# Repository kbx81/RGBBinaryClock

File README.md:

# kbx's RGB Binary Clock

RGB Binary Clock project files - PCB and source

_It's probably more than what you're thinking..._

## Another binary clock? Why?

I have to start by giving credit where credit is due. The
 [Boldport Club](http://boldport.club), over the last couple of years, has
 motivated me to dwell back into the world of electronics, at least as a
 hobbyist. Both the kits themselves and the other members in the club are
 amazing and helped inspire me to make something...so I began working on this
 project. Some inspiration is taken from
 [Touchy, BPC Project #7](https://www.boldport.com/products/touchy); this kit
 enabled me to learn more about and actually experiment with capacitive touch.
 It was clear early on that this would be a nice touch (pun intended) to add to
 this project; visually, it is cleaner, it reduces the number of parts and, as a
 result, it reduces the cost.

That said, the world probably doesn't need another (binary) clock. There are
 plenty of them--all different shapes and sizes--so why build another one?

This project was started with two main goals in mind: I wanted a "simple"
 project I could use to help me get back into the world of electronics. The
 second goal I had in mind was to build up my comfort level with C and C++ -- I
 knew the language(s) but was never terribly comfortable with them. Building
 this helped me to achieve both of those goals and then some -- and I am quite
 happy with the result!

_But why a clock?_

It's fun to make LEDs blink. It's fun to play with microcontrollers. It's fun
 to build stuff. But a blinking LED or two or three isn't very meaningful. Nor
 is a nice microcontroller that just toggles a GPIO pin. If you're going to
 build something, why not make it at least modestly useful? And why not build it
 in a unique way that's neat to look at and/or watch?

The idea for this came from an old electronics kit I put together probably
 around twenty or so years ago (and it still works today!). I liked the kit but
 it was somehow lacking. Probably the most obvious problem was that, in a dark
 bedroom, the display was too bright. It was a simple, 12-hour-only binary
 clock, built on 4000-series CMOS logic. Now, there's nothing wrong with that,
 but...it's 2018 now. Let's take it up a notch or ten.

## How do you take a binary clock up a notch (or ten)?

First, you can add some color. A lot of color. In fact, you can pick the colors
 you want it to use...up to eight times over. This binary clock has the ability
 to gradually shift colors over the course of each day. Bits can even fade in
 and out as they change. It's all about the eye candy in this regard.

Second, it can do more than just tell the time -- it'll tell you the date and
 temperature, too! There is even a timer/counter mode. What's more, you can
 choose the format for it all: the clock can display in a 12 or 24 hour format,
 the temperature can display in degrees Celsius or degrees Fahrenheit, and (most
 importantly) it can display all of these values in either binary-coded decimal
 (BCD) or good old-fashioned binary. You get to choose the formats you prefer
 and they can be changed easily at any time.

Next, the display brightness issue had to be addressed -- it has a
 phototransistor which is used to determine the amount of ambient light around
 it and the display will dim as the light level around it diminishes. This is
 great if you want to keep it near you at night while you sleep.

Another cool bit is that it uses capacitive sense touch keys for buttons; the
 kit it is based on had mechanical, fixed-function buttons. If you haven't seen
 or used capsense technology before, you'll find it's pretty cool and adds a
 little extra uniqueness to the clock, too.

A CR2032 coin-cell battery back-up can be installed to keep the time valid in
 the event that the board loses power. Version 4 of the hardware also includes a
 super capacitor, eliminating the need for the battery; even so, both can be
 installed, adding flexibility to the build.

Finally--and one could argue that no clock is complete without one--it has an
 alarm! The alarm can be set to beep at any of the eight times the user sets.
 There is also an hourly chime that one can enable which will beep out each hour
 in binary using high and/or low pitch tones...so you can hear the time when
 you're in another room! The display can be configured to blink when an alarm
 occurs. Version 4 of the clock also includes extra pin headers, some pins of
 which can be used as inputs to trigger the alarm from an external device.

## Great, but what makes it tick?

The "brain" is an STM32F072 microcontroller. This MCU alone has everything
 that's necessary to have a functional time clock -- even a temperature sensor
 as a bonus. Still, it might not be quite as accurate as some of us would like.
 For those folks, there are footprints for some additional ICs to improve the
 accuracy of the time and/or temperature sensing.

Version 2 boards have footprints for I2C devices:
* A Maxim DS3231
* An LM75 (or compatible)
* A Microchip MCP9808

Version 3+ boards have footprints for SPI devices:
* A Maxim DS3234
* An LM74
* A Maxim DS1722

Why footprints for both temperature sensors and the RTCs? The DS323x is somewhat
 expensive and it's possible that one might want more accurate temperature
 sensing abilities but isn't as concerned with the accuracy of the clock. It
 should be noted that the DS323x devices have temperature sensors built in and
 the application will use this sensor if a DS323x is installed but one of the
 other external temperature sensors is not.

Beyond the MCU itself, the board has 25 RGB LEDs on it; 24 of them form the main
 display and they are connected to TLC5947 (pre-v4) or TLC5951 (v4+)
 constant-current PWM drivers. The MCU uses its SPI1 to communicate with these
 drivers. The remaining RGB LED is used as a "status" LED and it is connected
 (through FET drivers) to GPIO pins on the MCU. These pins double as timer
 output channels, meaning they can also generate a PWM signal, enabling the
 dimming of the status LED elements, as well.

The beeper is connected (also through a FET driver) to yet another GPIO pin
 that doubles as a timer output channel; this enables the beeper to generate a
 wide range of tones or even play a tune!

The phototransistor is connected to the MCU's ADC channel zero.

Two USARTs are exposed via pin headers on the right side of the board: USART1
 is brought out on a standard six pin header as is commonly found on many
 devices while USART2 is connected to an RS-485 line driver enabling
 communication on an RS-485 bus. Through this interface, the application is able
 to receive a DMX-512 signal so the LEDs can each be individually controlled
 from an entertainment lighting console (or other application that speaks this
 protocol), enabling another whole realm of possibilities...

## How do I get or build one?

In this repository you'll find everything needed to put one together. It is
 divided into two major parts: hardware and software (source). The `hardware`
 directory contains the [KiCad](http://kicad.org) project files used to create
 the printed circuit board. The `src` directory contains the source code needed
 to compile and run the application on the microcontroller. It is built on top
 of [libopencm3](http://libopencm3.org). Finally, then `bin` directory contains
 compiled binary files you may flash directly onto the microcontroller...great
 for folks who want to solder something together but don't want to be bothered
 with compiling code!

Additional details regarding the hardware and software can be found in the
 `README.md` files located in each respective directory.

 **That's all for now...thanks for visiting!**

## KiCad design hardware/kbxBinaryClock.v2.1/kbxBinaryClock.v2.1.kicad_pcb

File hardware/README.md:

# kbx's RGB Binary Clock

RGB Binary Clock PCB project files for KiCad (v4/v5)

## How do I get PCBs made for this?

Detailing the process is a bit outside of what I plan to discuss here. There are
 plenty of resources out around the web already that will do a better job of
 explaining this process than I can. That said, there's not much to it -- the
 files you need are here and all you need to do (more or less) is upload them
 to your PCB fabricator of choice and, after a few days, they'll ship them
 to you. I've used [OSHPark](http://oshpark.com) for the prototypes and I can
 assure you that they turn out fantastic (purple) boards.

As the vast majority of the components on this board are surface-mount parts,
 hot air is a fun approach for soldering it all together. If you go this route
 (and especially if you plan to build more than one of them), you'll likely want
 to have a stencil made to help with the placement of solder paste onto the
 board. I've used [OSHStencils](http://oshstencils.com) for this and they are
 very quick and do a wonderful job.

**Important**: The TLC5947 and TLC5951 LED driver ICs have a thermal relief (aka
 exposed) pad on their underside; this will not be possible to solder without a
 hot air soldering station or reflow oven. At low current/intensity levels, this
 shouldn't be a problem, but if you want your LEDs to be really bright, this
 could present an issue as the drivers will overheat quickly. Be careful!

## If I get boards made, how do I build it?

All the components are listed in the KiCad project files here; one can also find
 a bill of materials file named `kbxBinaryClock.bom.vX.csv` containing this
 list. For "unusual" parts (things that aren't resistors or capacitors) I've
 noted a suggested part number that should serve as a point of reference to help
 you find your own.

Before you order parts, be sure to read through the build notes below!

Once you have your boards and parts, there are at least a couple of different
 ways you can build the clock. Below are build notes.

## Build notes

### Before you begin...

...you need to determine:
1. Which version of the clock will you build? The answer should be "version 4"
 unless there is a specific reason you want/need an earlier version.
1. What will your time source be -- the STM32's RTC or the DS323x? The DS323x
 will provide the best accuracy. That said, these ICs add approximately $10 USD
 to the cost of the device. If you're purchasing them, be sure you're ordering
 the one that matches the version of the hardware you're planning on building!
1. What temperature sensor will you use -- the STM32's internal sensor, the
 DS323x's sensor, or a dedicated sensor? The DS1621/LM75/MCP9804/DS1722/LM74
 dedicated sensors will provide the best accuracy; however, if one of these ICs
 is not installed but a DS323x *is* installed, the app will use the DS323x's
 sensor. Note that, while the PCBs have footprints for more than one temperature
 sensor, only **one** of them may be installed at a time.
1. Solder-bridge/jumper settings. These are hardware version specific but *must*
 be set properly before you begin using the clock. More details are below...but
 don't forget about these!

Once you've settled on the items above, read on (below) for more detail and
 specifics regarding the build.

### Build details

#### External RTC:

The external RTC--the DS3231 (hardware version 2.x) or the DS3234 (hardware
 version 3.x+)--adds a level of precision to the clock that is likely difficult
 to achieve with the STM32's internal RTC alone. These RTC ICs are designed to
 drift less than two minutes _per year_. It's possible that your STM32 hardware
 could end up being this accurate, but it's more likely that it will not be.
 Install this IC if you want a clock that is as accurate as is reasonably
 possible. Note that this IC also has a built-in temperature sensor (that's part
 of how it maintains its precision) that the application will use if it is
 installed and the other external temperature sensor (below) is _not_ installed.

If you install a DS3231/DS3234 on your clock, **do not install**:
 - Hardware v2.x: `C6`, `R8`
 - Hardware v3.x: `C6`, `R19`
 - Hardware v4.x: `C5`, `R3`

#### External temperature sensors:
**U7 and U8 (all hardware versions)**

A challenge with using the STM32's internal temperature sensor is that the
 sensor typically reads a few degrees higher than the temperature around the
 MCU itself. This is because the die, where the sensor is located, is usually
 just a little bit warmer then the package around it. An easy workaround is to
 just subtract a few degrees from the reading -- hence the calibration item
 you'll find in the application's menu structure. It works, but it requires
 someone to tweak it as each chip is likely to be a little different. Naturally,
 this takes away from its accuracy.

Installing an external temperature sensor is a great solution to this problem.
 The application will prefer an external sensor if one is installed; it first
 prefers one of the dedicated temperature sensors. If not installed, it will try
 to use the sensor integrated into the DS323x, should one be installed. If these
 all fail, it will use the STM32's internal sensor as a last resort.

**IMPORTANT NOTE: the PCBs (all hardware versions) have footprints for two
 external temperature sensor ICs. ONLY INSTALL ONE of them. DO NOT INSTALL
 BOTH.** If you install both, neither of them will work and you may cause damage
 to them or to other ICs on the board.

#### RS-485 transceiver:
**U9** (hardware v2.x and v3.x)\
**U6** (hardware v4.x)

This part will enable the the second USART in the STM32 MCU to be used to
 communicate on an RS-485 bus. The original intention for this feature was to
 enable the device to receive a DMX-512 signal from an entertainment lighting
 console. With some development, it could also be used (for example) to
 synchronize a number of clocks with each other. This interface is more of a toy
 and has no impact on how the clock itself will function. You'll likely want to
 leave it off of the board unless you have a specific plan to use it for
 something.

#### Buzzer/beeper components:
**BZ1, D1, Q1, R1** (hardware v2.x and v3.x)\
**BZ1, D2, Q2, R19** (hardware v4.x)

If you don't want your clock to be able to make any noise at all, it is safe to
 leave these parts off of your board. It'll be sad, but it'll work just fine.

#### Current drive control components:
**Q6 through Q11, R21 through R24, R26 through R29, R31 through R34,
 R36 and R37** (hardware v2.x)\
**Q6 through Q11, R20 through R23, R25 through R28, R30 through R33,
 R35 and R36** (hardware v3.x)\
(Not applicable to hardware v4.x)

These parts enable some software control over the constant-current mechanism in
 the TLC5947 PWM drivers. They enable, in a sense, a "master dimmer" control
 over the display as a whole. Their state can be defined through one of the menu
 options within the application. While not implemented just yet, future software
 versions might exercise them automatically, such as when the ambient light
 level changes.

#### Status LED components:
**LED25, LED26, Q2 through Q4, R2 through R7** (hardware v2.x and v3.x)\
**LED25, LED26, Q3 through Q5, R20 through R22, R25 through R27** (hardware v4.x)

The status LED is not typically used during normal operation, however it can be
 enabled as an AM/PM indicator if/when the clock is set in 12-hour mode. It can
 also provide troubleshooting information if your clock doesn't seem to be
 working. That said, it's not necessary unless you like LEDs as much as I do.

#### Reset/Boot buttons:

The reset and boot buttons are of course not required, but it is convenient if
 you plan to do any development with this platform on your own.

### Other requirements

#### 32.768 kHz crystal installation and connection:

A footprint for a 32.768 kHz crystal exists on all of the PCBs. It is used to
 drive the STM32's internal RTC mechanism. This crystal is particularly
 important if the DS323x IC is **not** installed; in this case, it must be
 connected to the MCU by creating a solder bridge across the appropriate two
 pads on `SB1`. Failure to do so--and if the DS323x is not installed--means the
 clock won't run (although things otherwise may seem to work).

If the DS323x **is** installed, `SB1` may be bridged so as to connect the
 DS323x's 32.768 kHz signal output to the STM32's OSC32 input. This is not
 required but it is recommended so that this MCU input isn't left floating. In
 addition, if `SB1` is bridged in this manner, the 32.768 kHz crystal (and its
 drive capacitors) should **not** be installed.

#### Phototransistor series resistors:
 **Q5, RV1, R9 and R10** (hardware v2.x)\
 **Q5, RV1, R8 and R9** (hardware v3.x)\
 **Q1, RV1, R4 and R5** (hardware v4.x)

The phototransistor enables the application to determine the amount of ambient
 light around the clock so it can adjust the overall display intensity
 accordingly. There is a variable resistor in series with a fixed resistor which
 allows some manual adjustment over the sensitivity of this mechanism. There is
 also a single fixed resistor in parallel with this configuration. It is not
 necessary to install all of these, however it won't hurt anything if you do.
 If the specified phototransistor is used, a single 100K to 150K resistor
 installed on the larger component number's (`R5`, `R9` or `R10`, depending on
 your hardware version) pads will probably work well.

#### Status LED:

If installing a status LED, install only LED25 **or** LED26. Do not install
 both.

### Solder Bridge Jumpers

#### 32.768 kHz Oscillator jumper
**SB1**

This jumper determines if the 32.768 kHz oscillator or the DS323x's 32.768 kHz
 output pin is connected to the STM32's OSC32_IN pin. If a DS323x is **not**
 installed on the board, it must be bridged so that the crystal's pin is
 connected to the OSC32_IN pin. Otherwise, it's best to bridge it to the
 DS323x's 32.768 kHz output pin. It can be determined with a close look at the
 PCB which position is which.

#### Reset Supervisor jumper
**SB2** (hardware v2.x and v3.x)\
**SB4** (hardware v4.x)

This jumper determines if the DS323x's reset supervisor output pin is connected
 to the STM32's NRST (not-reset) pin. This should be connected if the DS323x is
 installed, however it sometimes causes issues with flashing the MCU. If you
 installed a DS323x and are having difficulty flashing the MCU, try
 disconnecting this jumper until the flashing process is complete. Don't forget
 to reconnect it, though!

#### USART 1/USB VBUS jumpers
**SB2, SB3** (hardware v4.x)

These jumpers are on version 4+ boards and allow some configuration of which
 USART1 pin on the MCU is connected to the six-pin serial header. Because the
 processor expects USB VBUS on PA9, if you plan to use the USB port, SB2 should
 be bridged and SB3 should be bridged to put PB6 on the on the six-pin header.
 If you do not want/need to use the USB port and wish to flash the MCU via the
 six-pin header, SB2 must be left **open** and SB3 should be bridged to put PA9
 on the six-pin header.

#### RS-485 Terminator jumper
**SB5** (hardware v4.x)

Bridge this jumper to connect the terminating resistor across the RS-485
 transceiver's input/output pins. This is useful if the board is at the end of
 a RS-485 link.

## Before powering it on for the first time...

WAIT! you didn't plug it in yet, did you? Let's do some pre-flight checks to get
 ready to bring up your board!

It's important that we go over the board with a DMM (or at least a continuity
 tester) and check for any nasty shorts. Solder bridges and poor part placement
 are the typical causes of this and it's not uncommon to have them, particularly
 with so many surface-mount parts. We don't want our brand-new clock to let out
 the magic smoke before we even get to use it, do we? :)

Generally, it will suffice to check a few key areas for shorts. Since these are
 surface-mount ICs, it's not uncommon to have solder bridges between some of the
 pins after you've soldered it all together. Don't worry, we can get away
 without checking _all_ of them, but we _do_ need to check a few. Let's make a
 list so we can check them off:
* **Check for shorts between the output of the LDO and ground.** Put one of your
 DMM probes on the power connector's ground pin and the other on the LDO's
 heatsink (the top fin soldered to the board -- this is its 3.3-volt output). If
 you see they're shorted, you'll have to go hunting for the short. Start by
 checking the power pins around the STM32 processor. All of its Vcc and ground
 pins are right next to each other so this is the best place to look first.
* **Check for shorts between the LED cathode pins and ground.** Again, put one
 of your DMM probes on the power connector's ground pin and drag the other probe
 across each of the pins of the LEDs (this also serves as a chance to check for
 a short directly across the power input -- touch any of the anode pins to do
 so). If there's a short, touch-up the pins on the TLC59xx drivers. It might
 even be necessary to lift the driver IC completely off of the board (you have a
 hot air soldering station, right?). Due to the exposed/thermal pad on the
 bottom of the TLC59xx LED drivers, it's possible to have a solder bridge
 between one of the LED pins and ground. If this happens, the affected LED(s)
 will pop/fry/smoke/burn out immediately upon applying power to the board.
* **Check for shorts between the TLC59xx IREF pin and ground.** These pins are
 also adjacent and, if IREF is shorted to ground, too much current will flow
 through the LEDs (they'll be super bright and burn out quickly). This situation
 also increases the power dissipation of the TLC59xx drivers so they'll heat up
 unnecessarily. This also affects the power draw on the LDO so it'll get
 unnecessarily hot, too!
* **Check that the solder bridge "jumpers" are set correctly.** You didn't
 forget to bridge these as appropriate, did you? :) See the "Jumpers" section
 above for information on how they should be set.

Once you've confirmed everything above looks good, it should be reasonably safe
 to proceed to the next step -- flashing the firmware onto the STM32 processor!
 After we do this, we'll be able to more effectively identify any other
 soldering-related issues that could be affecting the clock's operation.

After you power on your board for the first time--and if nothing blows
 up--you'll need to flash the firmware onto the STM32 MCU. Hardware version 4.x
 of the clock also has a USB interface that may be used for this purpose, in
 addition to the SWD connection (P1/P2) or the serial interface on J2/J4. Either
 way, you'll need an appropriate adapter to do so. You can find the source,
 compiled binary files and flashing instructions in the `src` folder one level
 up in the repo's hierarchy. With the right tools in hand, this can be done in a
 couple of minutes.

If you're having trouble flashing the MCU, please see the next section.

## Troubleshooting

What's that? You couldn't flash the MCU? Or maybe it isn't working perfectly
 after you flashed the MCU? Uh oh...

As I've built...a few...of these to date, here is a list of common issues I've
 stumbled across as well as some notes on how to fix them.

If you're having trouble flashing the MCU, check these items first:
* If a DS323x is installed, is the reset supervisor jumper bridged? If so, this
 may be holding the STM32 in a reset state too long and your programmer is
 giving up. Open this jumper and try again.
* If there is no DS323x installed and/or the jumper is already open, check the
 data lines  between the port you're using (six-pin serial, USB, or SWD) and the
 processor. Perhaps there is another nasty solder bridge somewhere that's
 shorting one or more of the lines to Vcc, ground, or another adjacent pin. If
 you're using the USB interface on a version 4+ board, take a close look at D1
 and the physical USB port itself, as well.

If you flashed the MCU and it's now doing...something...but it doesn't seem
 right, here are some more common symptoms and how to fix them:

* **Status LED blinks white/gray but the main display is blank or flickers
 erratically.** This is indicative of some soldering problem on the SPI1 pins
 of the MCU or on one or more of the TLC59xx drivers. Take a close look at these
 pins and rework them as necessary.
* **One or more of the touch keys don't work.** Check the 1K resistors that sit
 between the touch keys and the MCU as well as the 47 nF sense capacitors.
 Again, also check the relevant pins on the MCU itself for shorts to adjacent
 pins.
* **It keeps making a ticking sound.** There's a problem with one or more of the
 touch keys -- see the item above.
* **The status LED alternates red and yellow.** You did not install a DS323x (or
 maybe you did and it's not working) and the STM32's RTC/LSE oscillator did not
 start within the expected amount of time. Check that `SB1` is bridged correctly
 and that the 32.768 kHz crystal and its bypass capacitors are installed and
 soldered correctly.
* **One or more of the LEDs are weird/mismatched colors.** This indicates that
 one or more of the LED pins on the TLC59xx drivers aren't soldered well. It
 could also mean that you have (a) bad LED(s) (maybe you overheated them or
 heated them for too long while soldering). Rework the relevant pins on the
 TLC59xx ICs and (hopefully) your LEDs will look normal afterwards. If not, you
 may want to try swapping out the affected LED(s).
* **One or more blocks of LEDs is brighter than the other block(s) of LEDs
 and/or one or more of the TLC59xx drivers is HOT along with the LDO.** Check
 the IREF pin on the (hot) driver below the block of LEDs that appears to be
 brighter than the others. It's probably shorted to ground.

## Known Issues and Noteworthy Items

You may have noticed the "hefty" 2-amp power supply rating on the board. Why is
 it so big? Well, each LED is rated for 20 milliamps (mA)...but are three colors
 per physical LED, adding up to 60 mA each. Then there are 25 LEDs...which adds
 up to 1500 mA -- a lot of current! We need a little extra for the other parts
 of the clock, so a 2 amp supply covers that nicely. That said, under normal use
 as a clock, it's unlikely that *all* of the LEDs would ever be fully on and
 driven at a full 20 mA each; in this case, you can likely get away with a power
 supply with a lesser rating. Under DMX-512 (or some other) control, however, it
 is possible that this situation could occur, so the goal was to ensure that the
 board could handle it. With that in mind, however, **if you wish to drive all
 of the LEDs at their full rated current of 20 mA for more than a few seconds at
 a time, you need to ensure three things happen:**
* The exposed pad on the LED driver ICs must be properly soldered to the PCB
* Heatsinks should be glued (with appropriate thermal epoxy) to the driver ICs
* The PCB should be manufactured with a 2 oz copper weight

Damage to your board and/or the parts on it may occur if the heat is not
 sufficiently dealt with -- the drivers can become VERY HOT!

Speaking of heat, said heat from the LED drivers can skew the temperature
 reading from the sensor on the board. This becomes more noticeable as the LEDs
 become brighter. Version 4.x of the PCBs includes footprints for additional
 2.54mm pin headers which could be used for mounting the temperature sensor(s)
 off of the main board.

Due to the nature of how the TLC5947 drivers work, frequent display refreshes
 (such as when LEDs are fading between colors and/or intensities) sometimes
 cause some faint flickering or pulsing of the LEDs. Version 4.x of the hardware
 resolves this issue by using TLC5951 drivers. These have a clock input to the
 PWM engine enabling writes to the data latches to be synchronized with PWM
 cycles. The result is smooth fading of the LEDs at all intensities with some
 additional benefits, as well!

## Legal stuff and License

The circuit schematics and PCBs found here are licensed under the
 [Creative Commons Attribution-ShareAlike 4.0 International License](http://creativecommons.org/licenses/by-sa/4.0/).

_Happy building!_

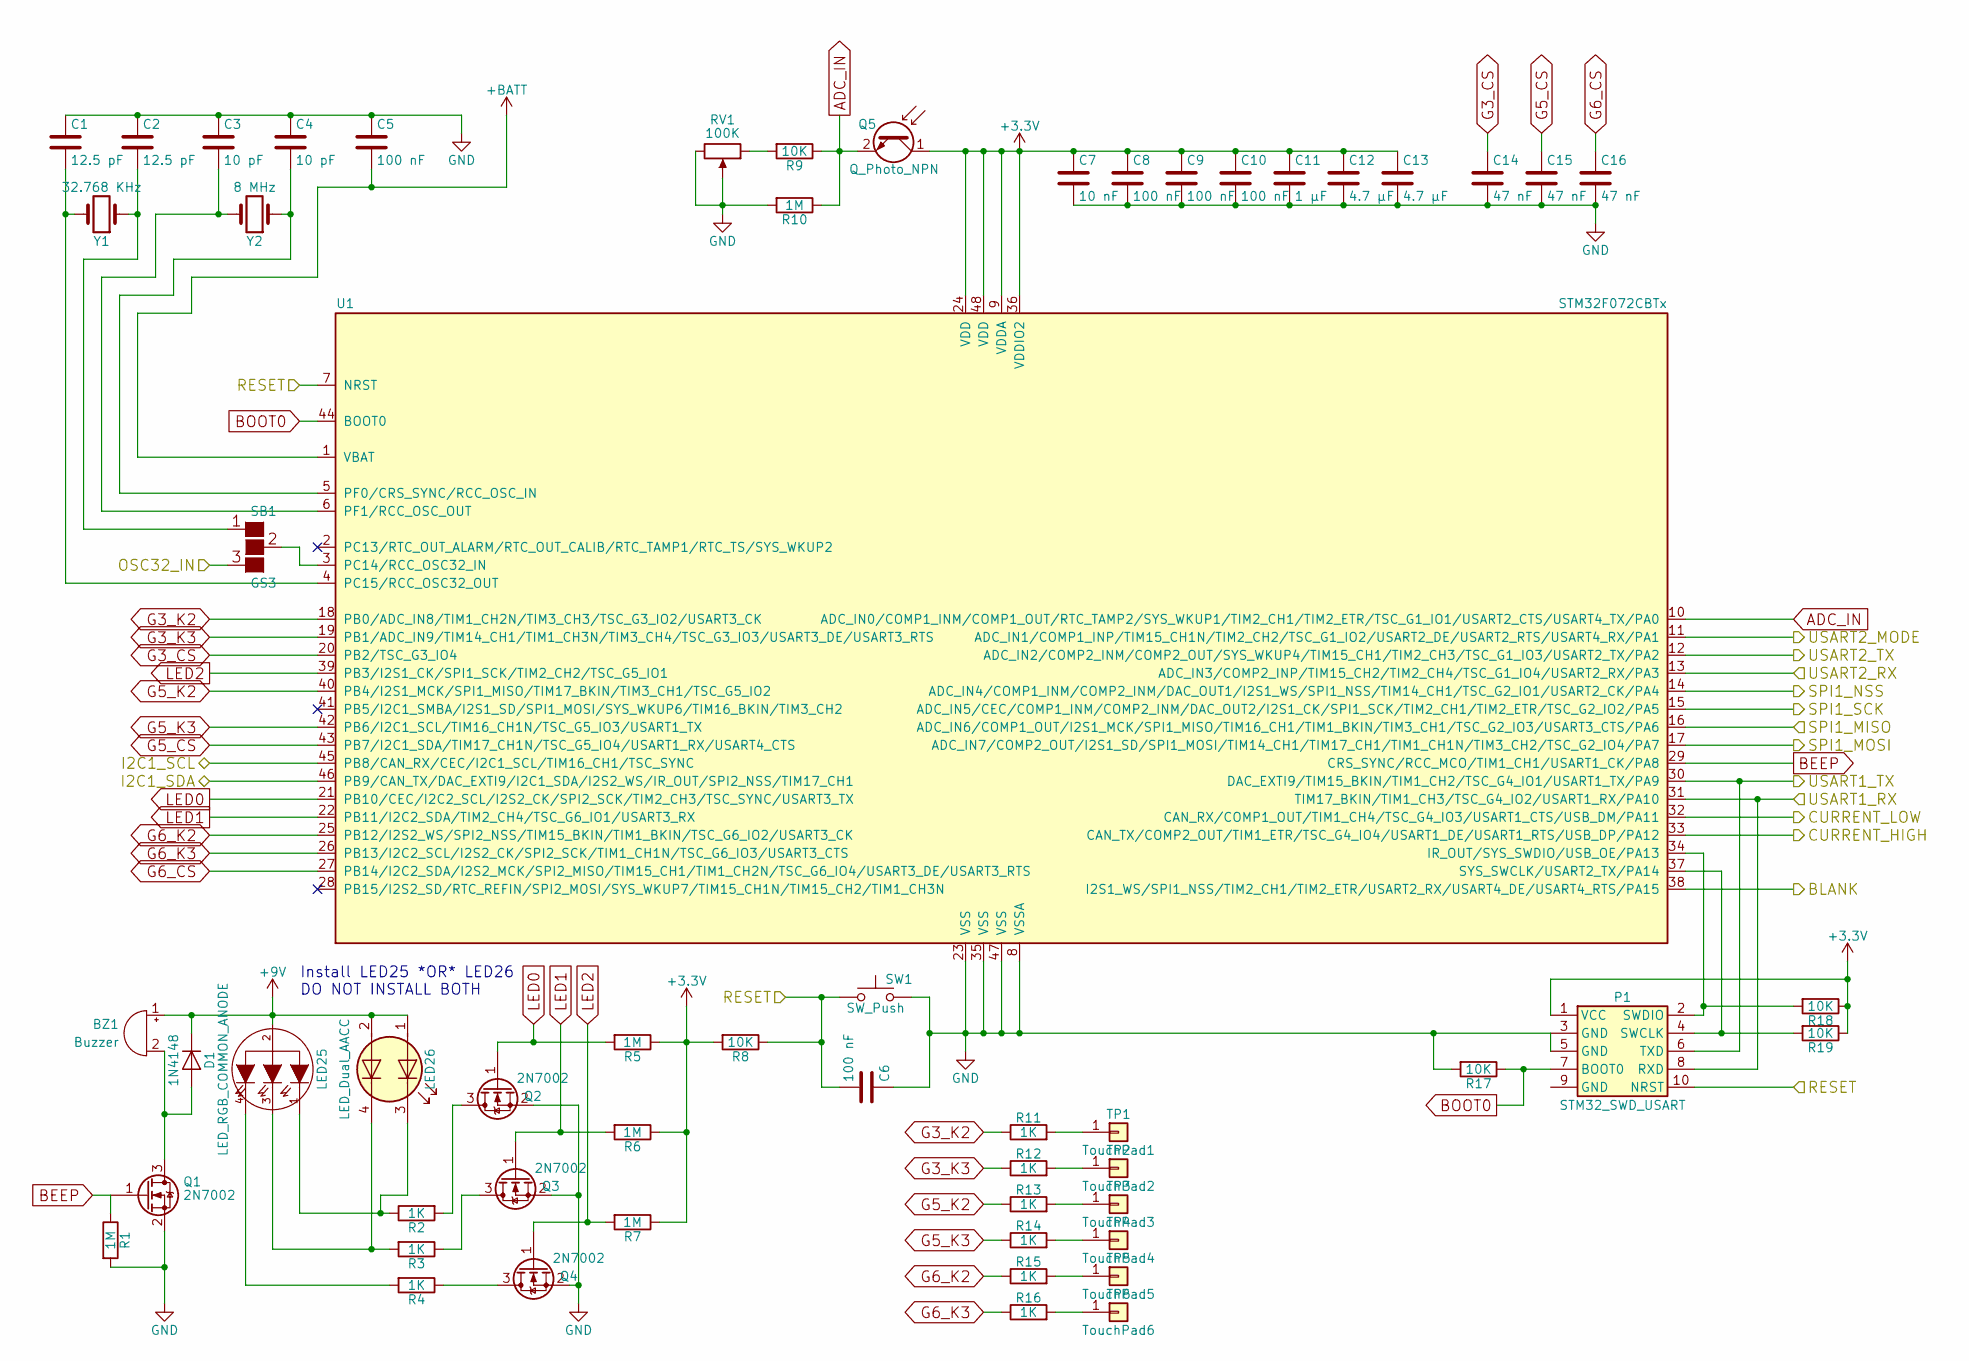
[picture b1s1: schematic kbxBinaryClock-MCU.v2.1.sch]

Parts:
BZ1: Buzzer; Buzzer_12x9.5RM7.6
C1, C2: 12.5 pF; C_0805
C3, C4: 10 pF; C_0805
C5, C6, C8, C9, C10: 100 nF; C_0805
C7: 10 nF; C_0805
C11: 1 µF; C_0805
C12, C13: 4.7 µF; C_0805
C14, C15, C16: 47 nF; C_0805
D1: 1N4148; D_SOD-123
LED25: LED_RGB_COMMON_ANODE; LED_D5.0mm-4
LED26: LED_Dual_AACC; LED_Cree-PLCC4_3.2x2.8mm_CCW
P1: STM32_SWD_USART; Pin_Header_Straight_2x05_Pitch1.27mm_SMD
Q1, Q2, Q3, Q4: 2N7002; SOT-23
Q5: Q_Photo_NPN; LED_D5.0mm
R1, R5, R6, R7, R10: 1M; R_0805
R2, R3, R4, R11, R12, R13, R14, R15, R16: 1K; R_0805
R8, R9, R17, R18, R19: 10K; R_0805
RV1: 100K; Potentiometer_Trimmer_Vishay_TS53YJ
SB1: GS3
SW1: SW_Push; SW_SPST_KMR2
TP1: TouchPad1
TP2: TouchPad2; TouchPad1
TP3: TouchPad3; TouchPad1
TP4: TouchPad4; TouchPad1
TP5: TouchPad5; TouchPad1
TP6: TouchPad6; TouchPad1
U1: STM32F072CBTx; LQFP-48_7x7mm_Pitch0.5mm
Y1: 32.768 KHz; Crystal_SMD_3215-2pin_3.2x1.5mm
Y2: 8 MHz; Crystal_SMD_5032-4pin_5.0x3.2mm

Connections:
+3V3: C7.1, C8.1, C9.1, C10.1, C11.1, C12.1, C13.1, P1.1 (VCC), Q5.1 (C), R5.1, R6.1, R7.1, R8.2, R18.1, R19.1, U1.9 (VDDA), U1.24 (VDD), U1.36 (VDDIO2), U1.48 (VDD); also elsewhere on the board
+9V: BZ1.1 (-), D1.1 (K), LED25.2 (COMMON), LED26.1 (A1), LED26.2 (A2); also elsewhere on the board
+BATT: C5.2, U1.1 (VBAT); also elsewhere on the board
/Display/BLANK: U1.38 (I2S1_WS/SPI1_NSS/TIM2_CH1/TIM2_ETR/USAR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); also elsewhere on the board
/Display/CURRENT_HIGH: U1.33 (CAN_TX/COMP2_OUT/TIM1_ETR/TSC_G4_IO4/US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); also elsewhere on the board
/Display/CURRENT_LOW: U1.32 (CAN_RX/COMP1_OUT/TIM1_CH4/TSC_G4_IO3/US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); also elsewhere on the board
/Display/SPI1_MISO: U1.16 (ADC_IN6/COMP1_OUT/I2S1_MCK/SPI1_MISO/TI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); also elsewhere on the board
/Display/SPI1_MOSI: U1.17 (ADC_IN7/COMP2_OUT/I2S1_SD/SPI1_MOSI/TIM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); also elsewhere on the board
/Display/SPI1_NSS: U1.14 (ADC_IN4/COMP1_INM/COMP2_INM/DAC_OUT1/I2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); also elsewhere on the board
/Display/SPI1_SCK: U1.15 (ADC_IN5/CEC/COMP1_INM/COMP2_INM/DAC_OUT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); also elsewhere on the board
/MCU/I2C1_SCL: U1.45 (PB8/CAN_RX/CEC/I2C1_SCL/TIM16_CH1/TSC_S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); also elsewhere on the board
/MCU/I2C1_SDA: U1.46 (PB9/CAN_TX/DAC_EXTI9/I2C1_SDA/I2S2_WS/I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); also elsewhere on the board
/MCU/OSC32_IN: SB1.3 (G3); also elsewhere on the board
/MCU/RESET: C6.2, P1.10 (NRST), R8.1, SW1.1, U1.7 (NRST); also elsewhere on the board
/MCU/USART1_RX: P1.8 (RXD), U1.31 (TIM17_BKIN/TIM1_CH3/TSC_G4_IO2/USART1_R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); also elsewhere on the board
/MCU/USART1_TX: P1.6 (TXD), U1.30 (DAC_EXTI9/TIM15_BKIN/TIM1_CH2/TSC_G4_IO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); also elsewhere on the board
/MCU/USART2_MODE: U1.11 (ADC_IN1/COMP1_INP/TIM15_CH1N/TIM2_CH2/T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); also elsewhere on the board
/MCU/USART2_RX: U1.13 (ADC_IN3/COMP2_INP/TIM15_CH2/TIM2_CH4/TS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); also elsewhere on the board
/MCU/USART2_TX: U1.12 (ADC_IN2/COMP2_INM/COMP2_OUT/SYS_WKUP4/T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); also elsewhere on the board
ADC_IN: Q5.2 (E), R9.1, R10.1, U1.10 (ADC_IN0/COMP1_INM/COMP1_OUT/RTC_TAMP2/S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)
BEEP: Q1.1 (G), R1.1, U1.29 (CRS_SYNC/RCC_MCO/TIM1_CH1/USART1_CK/PA8)
BOOT0: P1.7 (BOOT0), R17.1, U1.44 (BOOT0)
G3_CS: C14.1, U1.20 (PB2/TSC_G3_IO4)
G3_K2: R11.1, U1.18 (PB0/ADC_IN8/TIM1_CH2N/TIM3_CH3/TSC_G3_I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)
G3_K3: R12.1, U1.19 (PB1/ADC_IN9/TIM14_CH1/TIM1_CH3N/TIM3_CH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)
G5_CS: C15.1, U1.43 (PB7/I2C1_SDA/TIM17_CH1N/TSC_G5_IO4/USAR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)
G5_K2: R13.1, U1.40 (PB4/I2S1_MCK/SPI1_MISO/TIM17_BKIN/TIM3_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)
G5_K3: R14.1, U1.42 (PB6/I2C1_SCL/TIM16_CH1N/TSC_G5_IO3/USAR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)
G6_CS: C16.1, U1.27 (PB14/I2C2_SDA/I2S2_MCK/SPI2_MISO/TIM15_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)
G6_K2: R15.1, U1.25 (PB12/I2S2_WS/SPI2_NSS/TIM15_BKIN/TIM1_B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)
G6_K3: R16.1, U1.26 (PB13/I2C2_SCL/I2S2_CK/SPI2_SCK/TIM1_CH1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)
GND: C1.1, C2.1, C3.1, C4.1, C5.1, C6.1, C7.2, C8.2, C9.2, C10.2, C11.2, C12.2, C13.2, C14.2, C15.2, C16.2, P1.3 (GND), P1.5 (GND), Q1.2 (S), Q2.2 (S), Q3.2 (S), Q4.2 (S), R1.2, R10.2, R17.2, RV1.2, RV1.3, SW1.2, U1.8 (VSSA), U1.23 (VSS), U1.35 (VSS), U1.47 (VSS); also elsewhere on the board
LED0: Q2.1 (G), R5.2, U1.21 (PB10/CEC/I2C2_SCL/I2S2_CK/SPI2_SCK/TIM2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)
LED1: Q3.1 (G), R6.2, U1.22 (PB11/I2C2_SDA/TIM2_CH4/TSC_G6_IO1/USART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)
LED2: Q4.1 (G), R7.2, U1.39 (PB3/I2S1_CK/SPI1_SCK/TIM2_CH2/TSC_G5_IO1)
unnamed: BZ1.2 (+), D1.2 (A), Q1.3 (D)
unnamed: C1.2, U1.4 (PC15/RCC_OSC32_OUT), Y1.2
unnamed: C2.2, SB1.1 (G1), Y1.1
unnamed: C3.2, U1.6 (PF1/RCC_OSC_OUT), Y2.2
unnamed: C4.2, U1.5 (PF0/CRS_SYNC/RCC_OSC_IN), Y2.1
unnamed: LED25.1 (RED), LED26.3 (K1), R2.1
unnamed: LED25.3 (GREEN), LED26.4 (K2), R3.2
unnamed: LED25.4 (BLUE), R4.2
unnamed: P1.2 (SWDIO), R18.2, U1.34 (IR_OUT/SYS_SWDIO/USB_OE/PA13)
unnamed: P1.4 (SWCLK), R19.2, U1.37 (SYS_SWCLK/USART2_TX/PA14)
unnamed: Q2.3 (D), R2.2
unnamed: Q3.3 (D), R3.1
unnamed: Q4.3 (D), R4.1
unnamed: R9.2, RV1.1
unnamed: R11.2, TP1.1
unnamed: R12.2, TP2.1
unnamed: R13.2, TP3.1
unnamed: R14.2, TP4.1
unnamed: R15.2, TP5.1
unnamed: R16.2, TP6.1
unnamed: SB1.2 (G2), U1.3 (PC14/RCC_OSC32_IN)

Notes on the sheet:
Install LED25 *OR* LED26 DO NOT INSTALL BOTH

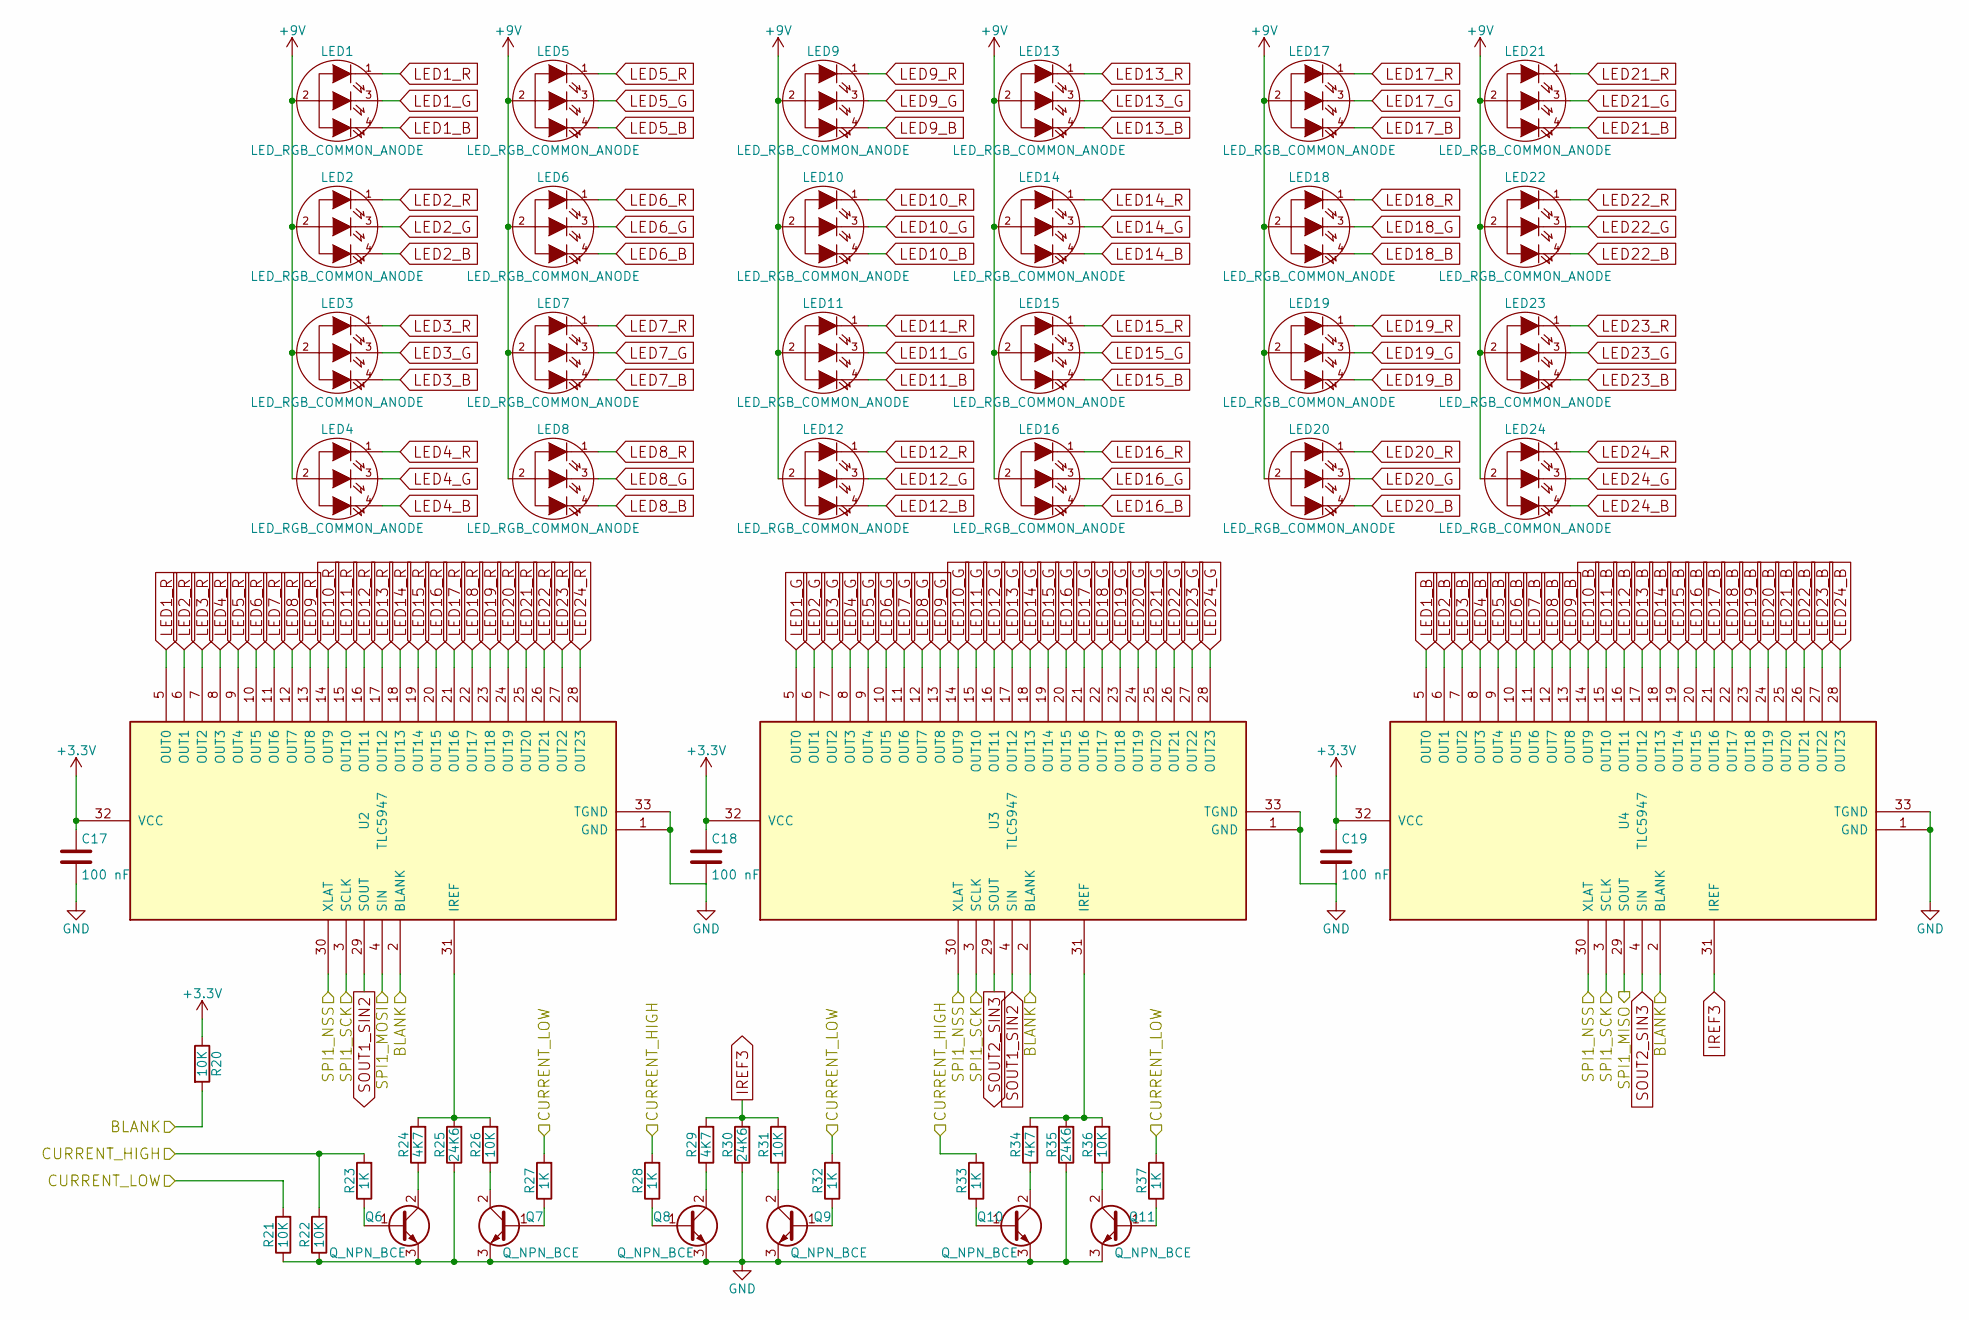
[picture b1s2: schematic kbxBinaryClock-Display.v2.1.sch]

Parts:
C17, C18, C19: 100 nF; C_0805
LED1, LED2, LED3, LED4, LED5, LED6, LED7, LED8, LED9, LED10, LED11, LED12, LED13, LED14, LED15, LED16, LED17, LED18, LED19, LED20, LED21, LED22, LED23, LED24: LED_RGB_COMMON_ANODE; LED_D5.0mm-4
Q6, Q7, Q8, Q9, Q10, Q11: Q_NPN_BCE; SOT-23
R20, R21, R22, R26, R31, R36: 10K; R_0805
R23, R27, R28, R32, R33, R37: 1K; R_0805
R24, R29, R34: 4K7; R_0805
R25, R30, R35: 24K6; R_0805
U2, U3, U4: TLC5947; HTSSOP-32_6.1x11mm_Pitch0.65mm_ThermalPad

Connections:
+3V3: C17.1, C18.1, C19.1, R20.1, U2.32 (VCC), U3.32 (VCC), U4.32 (VCC); also elsewhere on the board
+9V: LED1.2 (COMMON), LED2.2 (COMMON), LED3.2 (COMMON), LED4.2 (COMMON), LED5.2 (COMMON), LED6.2 (COMMON), LED7.2 (COMMON), LED8.2 (COMMON), LED9.2 (COMMON), LED10.2 (COMMON), LED11.2 (COMMON), LED12.2 (COMMON), LED13.2 (COMMON), LED14.2 (COMMON), LED15.2 (COMMON), LED16.2 (COMMON), LED17.2 (COMMON), LED18.2 (COMMON), LED19.2 (COMMON), LED20.2 (COMMON), LED21.2 (COMMON), LED22.2 (COMMON), LED23.2 (COMMON), LED24.2 (COMMON); also elsewhere on the board
/Display/BLANK: R20.2, U2.2 (BLANK), U3.2 (BLANK), U4.2 (BLANK); also elsewhere on the board
/Display/CURRENT_HIGH: R22.2, R23.2, R28.2, R33.2; also elsewhere on the board
/Display/CURRENT_LOW: R21.2, R27.2, R32.2, R37.2; also elsewhere on the board
/Display/SPI1_MISO: U4.29 (SOUT); also elsewhere on the board
/Display/SPI1_MOSI: U2.4 (SIN); also elsewhere on the board
/Display/SPI1_NSS: U2.30 (XLAT), U3.30 (XLAT), U4.30 (XLAT); also elsewhere on the board
/Display/SPI1_SCK: U2.3 (SCLK), U3.3 (SCLK), U4.3 (SCLK); also elsewhere on the board
GND: C17.2, C18.2, C19.2, Q6.3 (E), Q7.3 (E), Q8.3 (E), Q9.3 (E), Q10.3 (E), Q11.3 (E), R21.1, R22.1, R25.1, R30.1, R35.1, U2.1 (GND), U2.33 (TGND), U3.1 (GND), U3.33 (TGND), U4.1 (GND), U4.33 (TGND); also elsewhere on the board
IREF3: R29.2, R30.2, R31.2, U4.31 (IREF)
LED1_B: LED1.4 (BLUE), U4.5 (OUT0)
LED1_G: LED1.3 (GREEN), U3.5 (OUT0)
LED1_R: LED1.1 (RED), U2.5 (OUT0)
LED2_B: LED2.4 (BLUE), U4.6 (OUT1)
LED2_G: LED2.3 (GREEN), U3.6 (OUT1)
LED2_R: LED2.1 (RED), U2.6 (OUT1)
LED3_B: LED3.4 (BLUE), U4.7 (OUT2)
LED3_G: LED3.3 (GREEN), U3.7 (OUT2)
LED3_R: LED3.1 (RED), U2.7 (OUT2)
LED4_B: LED4.4 (BLUE), U4.8 (OUT3)
LED4_G: LED4.3 (GREEN), U3.8 (OUT3)
LED4_R: LED4.1 (RED), U2.8 (OUT3)
LED5_B: LED5.4 (BLUE), U4.9 (OUT4)
LED5_G: LED5.3 (GREEN), U3.9 (OUT4)
LED5_R: LED5.1 (RED), U2.9 (OUT4)
LED6_B: LED6.4 (BLUE), U4.10 (OUT5)
LED6_G: LED6.3 (GREEN), U3.10 (OUT5)
LED6_R: LED6.1 (RED), U2.10 (OUT5)
LED7_B: LED7.4 (BLUE), U4.11 (OUT6)
LED7_G: LED7.3 (GREEN), U3.11 (OUT6)
LED7_R: LED7.1 (RED), U2.11 (OUT6)
LED8_B: LED8.4 (BLUE), U4.12 (OUT7)
LED8_G: LED8.3 (GREEN), U3.12 (OUT7)
LED8_R: LED8.1 (RED), U2.12 (OUT7)
LED9_B: LED9.4 (BLUE), U4.13 (OUT8)
LED9_G: LED9.3 (GREEN), U3.13 (OUT8)
LED9_R: LED9.1 (RED), U2.13 (OUT8)
LED10_B: LED10.4 (BLUE), U4.14 (OUT9)
LED10_G: LED10.3 (GREEN), U3.14 (OUT9)
LED10_R: LED10.1 (RED), U2.14 (OUT9)
LED11_B: LED11.4 (BLUE), U4.15 (OUT10)
LED11_G: LED11.3 (GREEN), U3.15 (OUT10)
LED11_R: LED11.1 (RED), U2.15 (OUT10)
LED12_B: LED12.4 (BLUE), U4.16 (OUT11)
LED12_G: LED12.3 (GREEN), U3.16 (OUT11)
LED12_R: LED12.1 (RED), U2.16 (OUT11)
LED13_B: LED13.4 (BLUE), U4.17 (OUT12)
LED13_G: LED13.3 (GREEN), U3.17 (OUT12)
LED13_R: LED13.1 (RED), U2.17 (OUT12)
LED14_B: LED14.4 (BLUE), U4.18 (OUT13)
LED14_G: LED14.3 (GREEN), U3.18 (OUT13)
LED14_R: LED14.1 (RED), U2.18 (OUT13)
LED15_B: LED15.4 (BLUE), U4.19 (OUT14)
LED15_G: LED15.3 (GREEN), U3.19 (OUT14)
LED15_R: LED15.1 (RED), U2.19 (OUT14)
LED16_B: LED16.4 (BLUE), U4.20 (OUT15)
LED16_G: LED16.3 (GREEN), U3.20 (OUT15)
LED16_R: LED16.1 (RED), U2.20 (OUT15)
LED17_B: LED17.4 (BLUE), U4.21 (OUT16)
LED17_G: LED17.3 (GREEN), U3.21 (OUT16)
LED17_R: LED17.1 (RED), U2.21 (OUT16)
LED18_B: LED18.4 (BLUE), U4.22 (OUT17)
LED18_G: LED18.3 (GREEN), U3.22 (OUT17)
LED18_R: LED18.1 (RED), U2.22 (OUT17)
LED19_B: LED19.4 (BLUE), U4.23 (OUT18)
LED19_G: LED19.3 (GREEN), U3.23 (OUT18)
LED19_R: LED19.1 (RED), U2.23 (OUT18)
LED20_B: LED20.4 (BLUE), U4.24 (OUT19)
LED20_G: LED20.3 (GREEN), U3.24 (OUT19)
LED20_R: LED20.1 (RED), U2.24 (OUT19)
LED21_B: LED21.4 (BLUE), U4.25 (OUT20)
LED21_G: LED21.3 (GREEN), U3.25 (OUT20)
LED21_R: LED21.1 (RED), U2.25 (OUT20)
LED22_B: LED22.4 (BLUE), U4.26 (OUT21)
LED22_G: LED22.3 (GREEN), U3.26 (OUT21)
LED22_R: LED22.1 (RED), U2.26 (OUT21)
LED23_B: LED23.4 (BLUE), U4.27 (OUT22)
LED23_G: LED23.3 (GREEN), U3.27 (OUT22)
LED23_R: LED23.1 (RED), U2.27 (OUT22)
LED24_B: LED24.4 (BLUE), U4.28 (OUT23)
LED24_G: LED24.3 (GREEN), U3.28 (OUT23)
LED24_R: LED24.1 (RED), U2.28 (OUT23)
unnamed: Q6.1 (B), R23.1
unnamed: Q6.2 (C), R24.1
unnamed: Q7.1 (B), R27.1
unnamed: Q7.2 (C), R26.1
unnamed: Q8.1 (B), R28.1
unnamed: Q8.2 (C), R29.1
unnamed: Q9.1 (B), R32.1
unnamed: Q9.2 (C), R31.1
unnamed: Q10.1 (B), R33.1
unnamed: Q10.2 (C), R34.1
unnamed: Q11.1 (B), R37.1
unnamed: Q11.2 (C), R36.1
unnamed: R24.2, R25.2, R26.2, U2.31 (IREF)
unnamed: R34.2, R35.2, R36.2, U3.31 (IREF)
SOUT1_SIN2: U2.29 (SOUT), U3.4 (SIN)
SOUT2_SIN3: U3.29 (SOUT), U4.4 (SIN)

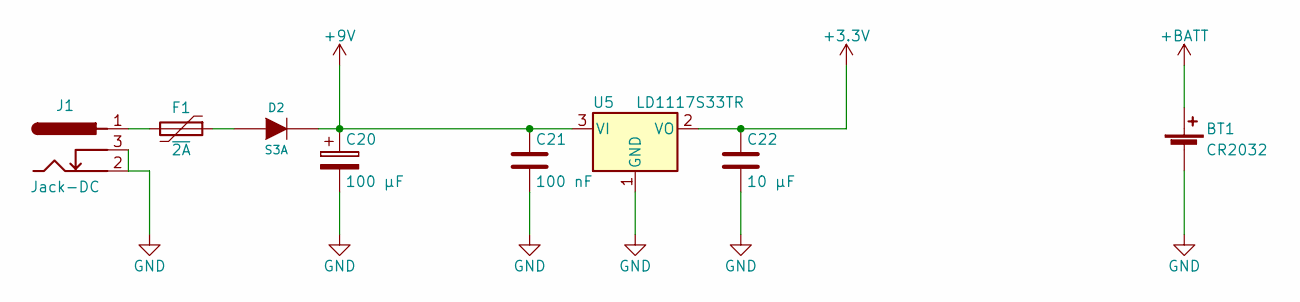
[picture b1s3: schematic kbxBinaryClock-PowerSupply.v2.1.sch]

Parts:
BT1: CR2032; Keystone_103_1x20mm-CoinCell
C20: 100 µF; CP_Elec_8x10
C21: 100 nF; C_0805
C22: 10 µF; C_0805
D2: S3A; D_SMC
F1: ~2A; Fuse_SMD2920
J1: Jack-DC; BARREL_JACK
U5: LD1117S33TR; TO-252-2

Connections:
+3V3: C22.1, U5.2 (VO); also elsewhere on the board
+9V: C20.1, C21.1, D2.2 (K), U5.3 (VI); also elsewhere on the board
+BATT: BT1.1 (+); also elsewhere on the board
GND: BT1.2 (-), C20.2, C21.2, C22.2, J1.2, J1.3, U5.1 (GND); also elsewhere on the board
unnamed: D2.1 (A), F1.1
unnamed: F1.2, J1.1

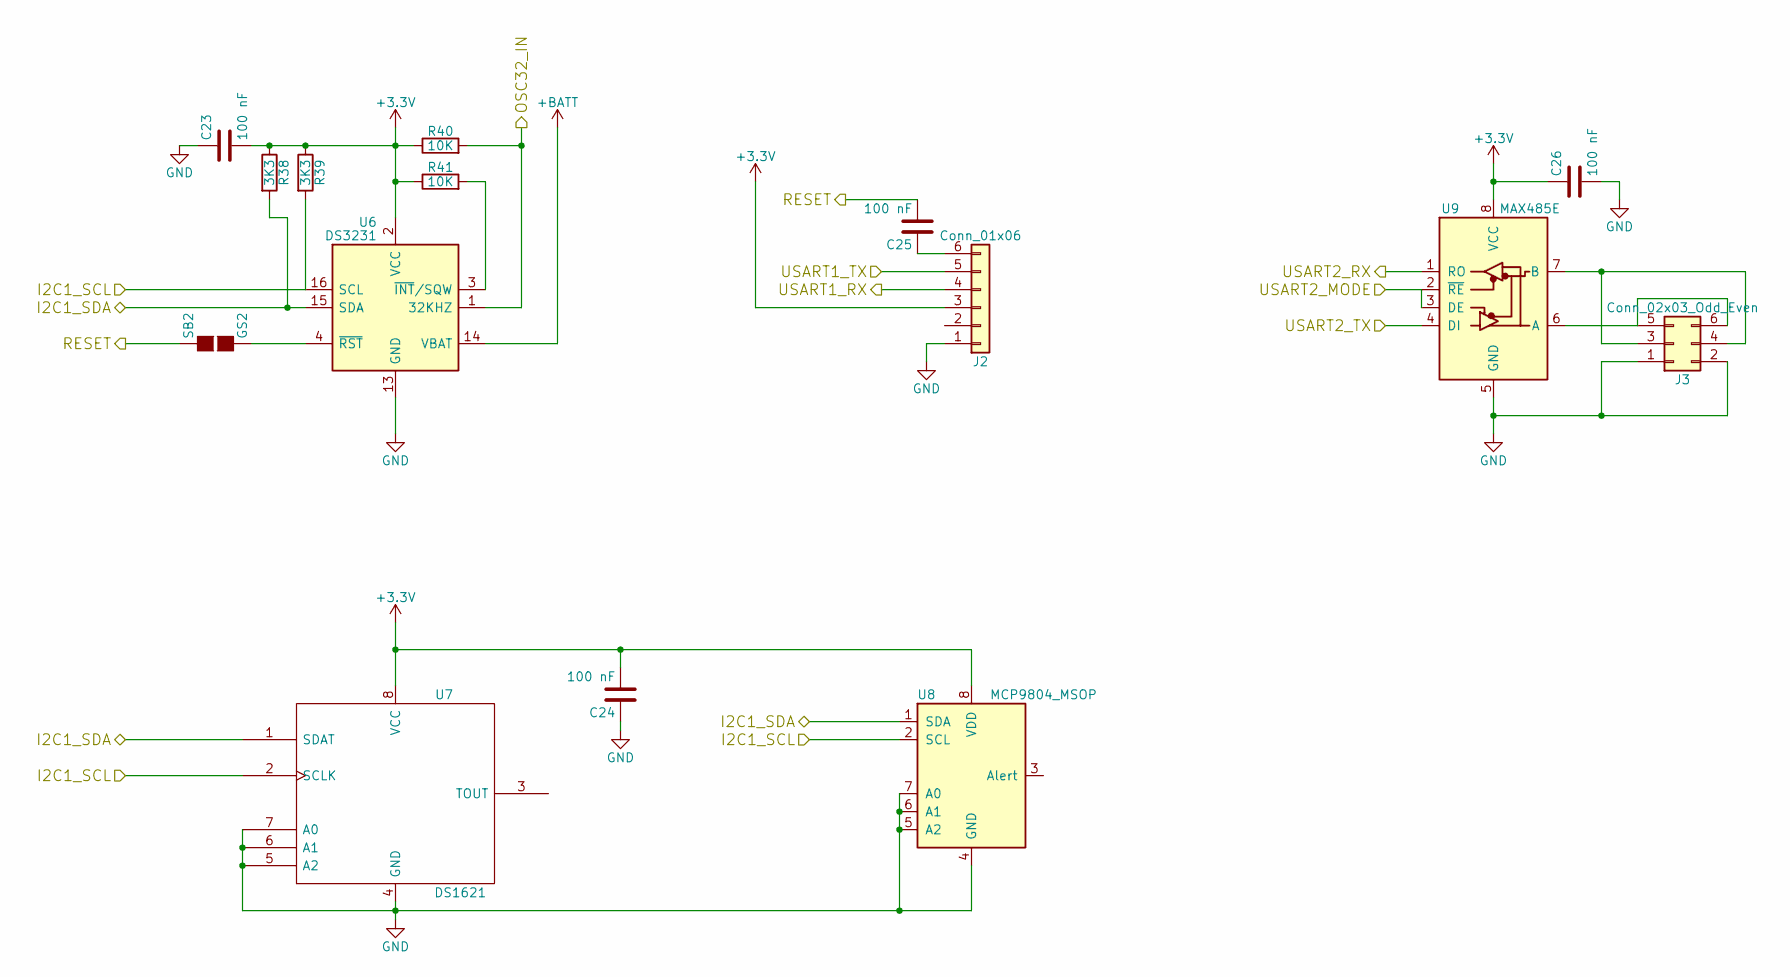
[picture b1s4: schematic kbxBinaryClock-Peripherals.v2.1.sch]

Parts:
C23, C24, C25, C26: 100 nF; C_0805
J2: Conn_01x06; Pin_Header_Straight_1x06_Pitch2.54mm
J3: Conn_02x03_Odd_Even; Pin_Header_Straight_2x03_Pitch2.54mm
R38, R39: 3K3; R_0805
R40, R41: 10K; R_0805
SB2: GS2
U6: DS3231; SOIC-16W_7.5x10.3mm_Pitch1.27mm
U7: DS1621; SOIC-8_3.9x4.9mm_Pitch1.27mm
U8: MCP9804_MSOP; MSOP-8_3x3mm_Pitch0.65mm
U9: MAX485E; SOIC-8_3.9x4.9mm_Pitch1.27mm

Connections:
+3V3: C23.2, C24.2, C26.1, J2.3, R38.1, R39.1, R40.1, R41.1, U6.2 (VCC), U7.8 (VCC), U8.8 (VDD), U9.8 (VCC); also elsewhere on the board
+BATT: U6.14 (VBAT); also elsewhere on the board
/MCU/I2C1_SCL: R39.2, U6.16 (SCL), U7.2 (SCLK), U8.2 (SCL); also elsewhere on the board
/MCU/I2C1_SDA: R38.2, U6.15 (SDA), U7.1 (SDAT), U8.1 (SDA); also elsewhere on the board
/MCU/OSC32_IN: R40.2, U6.1 (32KHZ); also elsewhere on the board
/MCU/RESET: C25.2, SB2.1 (G1); also elsewhere on the board
/MCU/USART1_RX: J2.4; also elsewhere on the board
/MCU/USART1_TX: J2.5; also elsewhere on the board
/MCU/USART2_MODE: U9.2 (~RE), U9.3 (DE); also elsewhere on the board
/MCU/USART2_RX: U9.1 (RO); also elsewhere on the board
/MCU/USART2_TX: U9.4 (DI); also elsewhere on the board
GND: C23.1, C24.1, C26.2, J2.1, J3.1, J3.2, U6.5 (NC), U6.6 (NC), U6.7 (NC), U6.8 (NC), U6.9 (NC), U6.10 (NC), U6.11 (NC), U6.12 (NC), U6.13 (GND), U7.4 (GND), U7.5 (A2), U7.6 (A1), U7.7 (A0), U8.4 (GND), U8.5 (A2), U8.6 (A1), U8.7 (A0), U9.5 (GND); also elsewhere on the board
unnamed: C25.1, J2.6
unnamed: J3.3, J3.4, U9.7 (B)
unnamed: J3.5, J3.6, U9.6 (A)
unnamed: R41.2, U6.3 (~INT~/SQW)
unnamed: SB2.2 (G2), U6.4 (~RST)

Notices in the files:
src/v1/Hardware.cpp:
(c)2017 by kbx81. See LICENSE for details.
This program is free software: you can redistribute it and/or modify
it under the terms of the GNU Lesser General Public License as published by
the Free Software Foundation, either version 3 of the License, or
(at your option) any later version.
hardware/README.md:
Legal stuff and License:
The circuit schematics and PCBs found here are licensed under the
[Creative Commons Attribution-ShareAlike 4.0 International License](http://creativecommons.org/licenses/by-sa/4.0/).
_Happy building!_
